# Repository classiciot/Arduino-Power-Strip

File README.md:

# Arduino-Power-Strip
Arduino-Power-Strip is a Arduino shield to control electrical devices

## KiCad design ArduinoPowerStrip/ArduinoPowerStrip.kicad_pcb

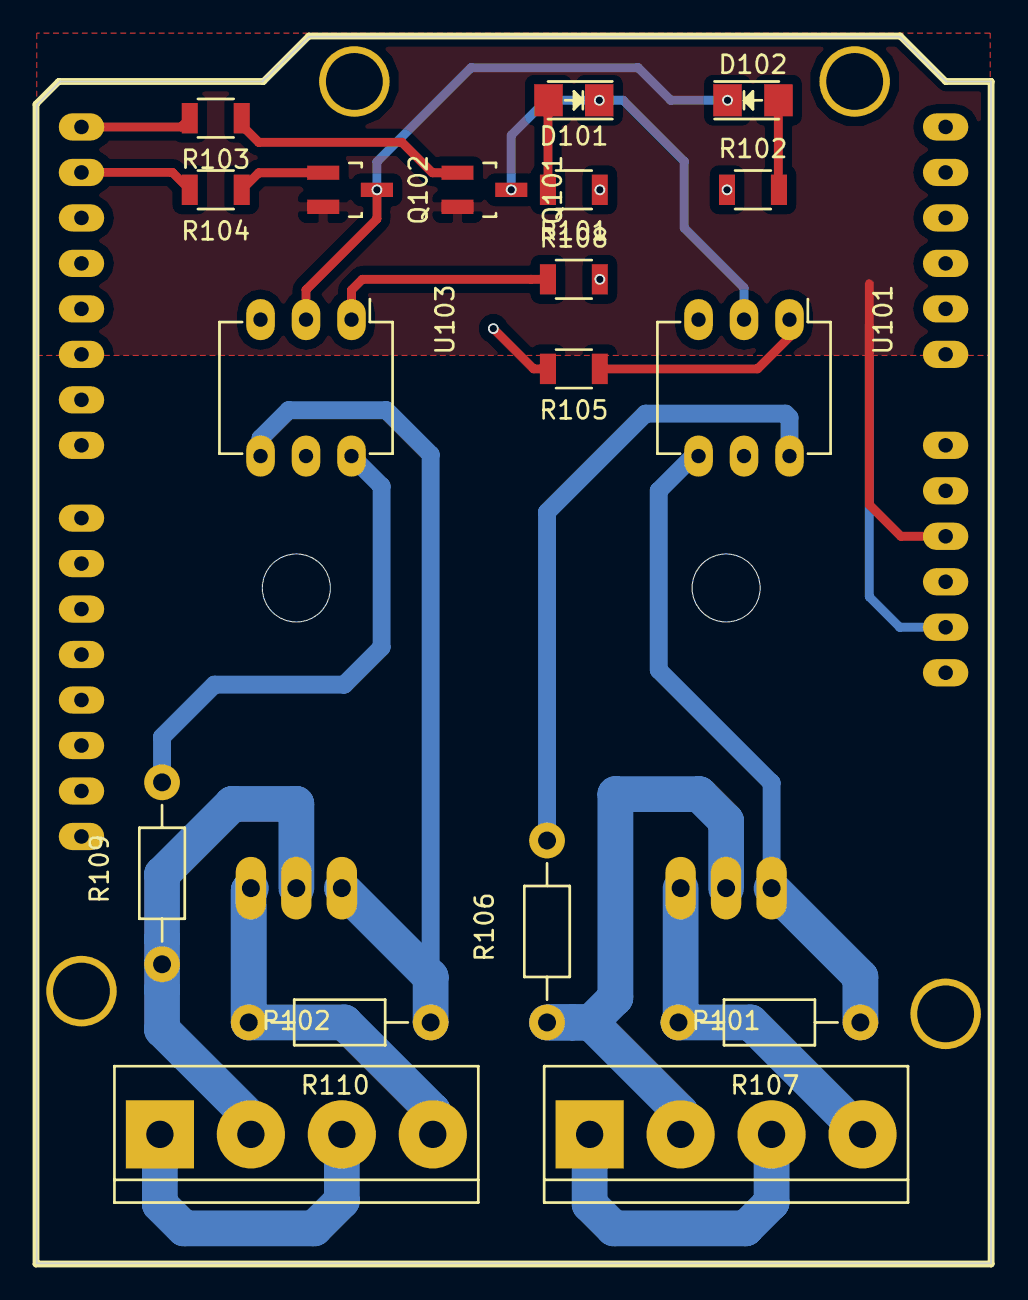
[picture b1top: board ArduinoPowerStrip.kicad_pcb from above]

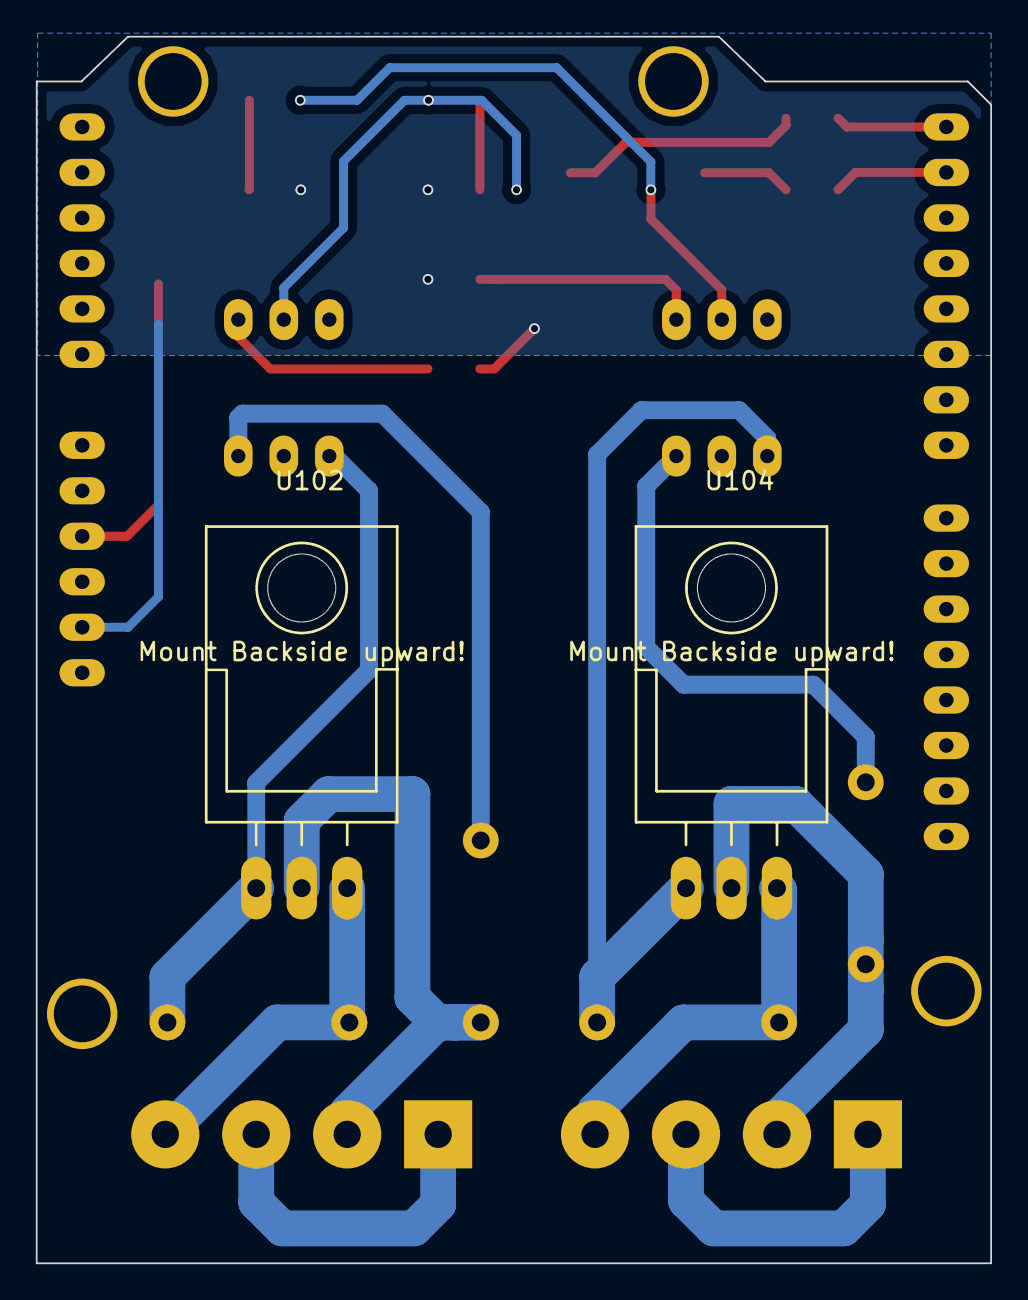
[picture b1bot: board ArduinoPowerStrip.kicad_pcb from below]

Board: 2 copper layers, 53.3 x 68.5 mm, 21 parts (2 on the bottom side), 22 nets.

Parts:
D101, D102: LED; LED_1206
P101: Con1; bornier4
P102: Con2; bornier4
Q101, Q102: BC847-SOT23; SOT-23_Handsoldering
R101, R102, R103, R104: 331; R_1206
R105, R108: 131; R_1206
R106, R109: 361; Resistor_Horizontal_RM10mm
R107, R110: 331; Resistor_Horizontal_RM10mm
SHIELD101: ARDUINO_SHIELD; ArduinoShield
U101, U103: MOC3041M; DIP-6_W7.62mm_LongPads
U102, U104: BTA06-600BW; TO-220_Neutral123_Horizontal_Reverse_LargePads

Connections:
/Gnd: Q101.2, Q102.2, SHIELD101.GND1
/Q1In: R103.2, SHIELD101.0
/Q1Out: D101.1, Q101.3, U101.2
/Q2In: R104.2, SHIELD101.1
/Q2Out: D102.1, Q102.3, U103.2
/Triac1L: P101.2, R106.1, U102.2
/Triac1N: P101.1, P101.3
/Triac1O: P101.4, R107.2, U102.1
/Triac2L: P102.2, R109.1, U104.2
/Triac2N: P102.1, P102.3
/Triac2O: P102.4, R110.2, U104.1
/Vcc: R101.1, R102.1, R105.2, R108.2, SHIELD101.3V3
unnamed: D101.2, R101.2
unnamed: D102.2, R102.2
unnamed: Q101.1, R103.1
unnamed: Q102.1, R104.1
unnamed: R105.1, U101.1
unnamed: R106.2, U101.6
unnamed: R107.1, U101.4, U102.3
unnamed: R108.1, U103.1
unnamed: R109.2, U103.6
unnamed: R110.1, U103.4, U104.3

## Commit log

2016-03-19 Importing the work
2016-03-20 Moved library to project folder
2016-03-20 Added datashets
2016-03-26 Initial draft of the final board
2016-03-28 Create gh-pages branch via GitHub
2016-03-29 Double sided board and separeted Power signals
2016-03-29 Added LED Indicators
